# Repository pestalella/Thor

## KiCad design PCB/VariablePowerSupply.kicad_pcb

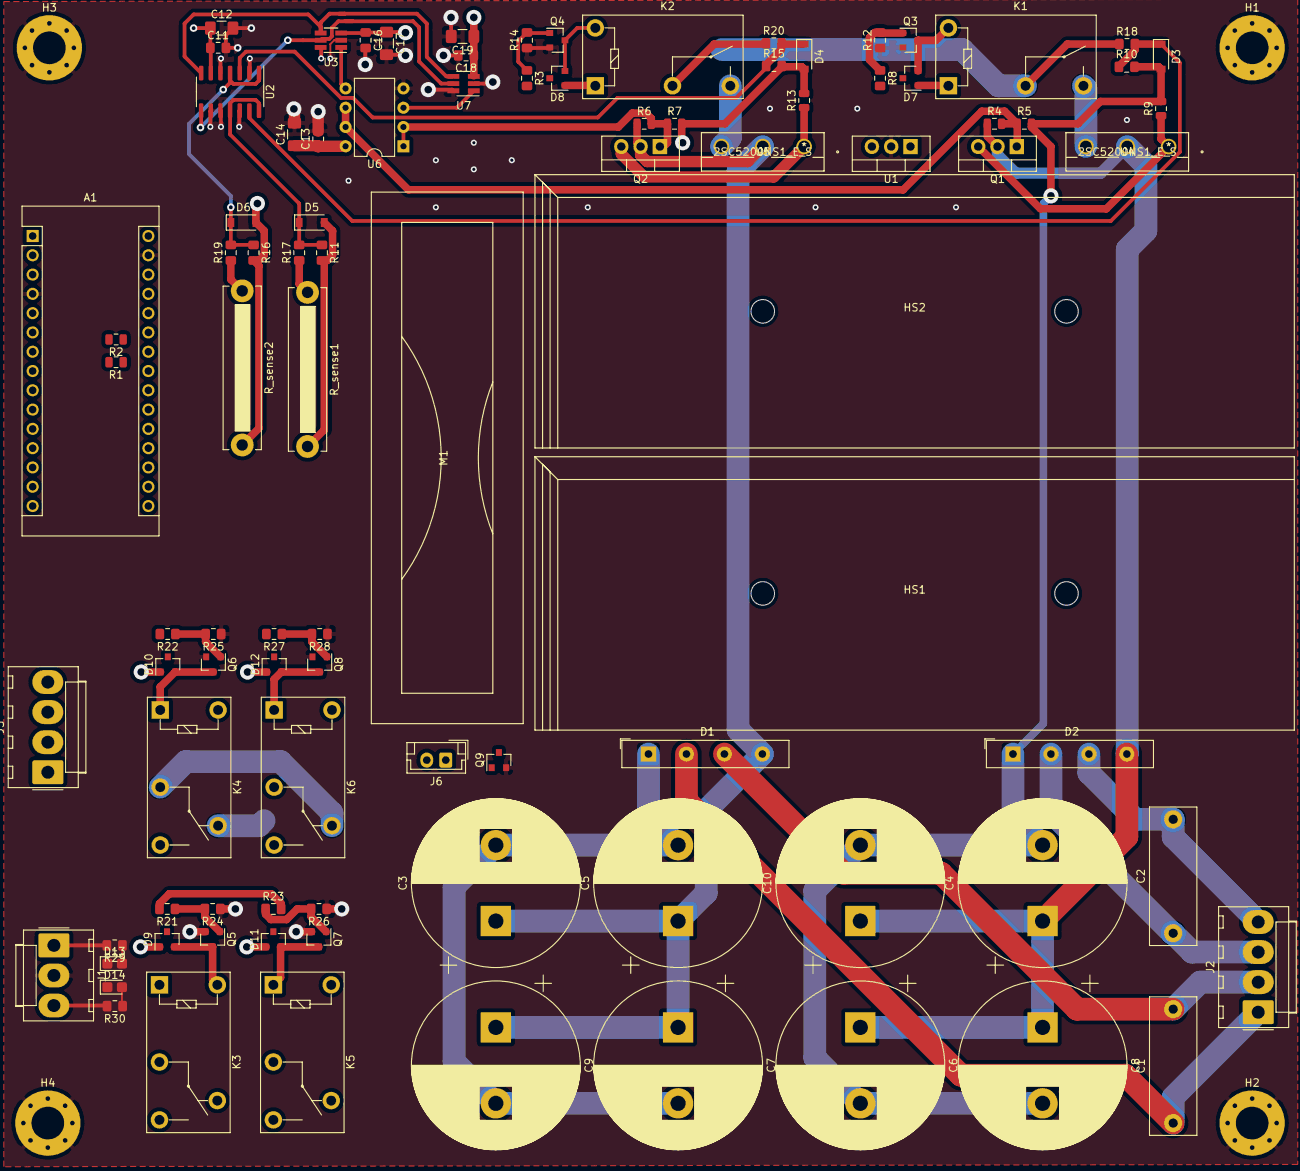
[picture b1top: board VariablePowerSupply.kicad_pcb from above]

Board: 4 copper layers, 98 parts (0 on the bottom side), 55 nets.

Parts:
A1: Arduino_Nano_v2.x; Arduino_Nano
C1, C2: C; C_Rect_L18.0mm_W6.0mm_P15.00mm_FKS3_FKP3
C3, C4, C5, C6, C7, C8, C9, C10: C; CP_Radial_D22.0mm_P10.00mm_SnapIn
C11, C13, C16, C18: 0.1uF; C_0805_2012Metric_Pad1.15x1.40mm_HandSolder
C12, C14, C17, C19: 10uF; C_1206_3216Metric_Pad1.42x1.75mm_HandSolder
D1, D2: D_Bridge_-AA+; Diode_Bridge_22.3x3.5x18.3mm_P5.0mm
D3, D4, D5, D6: 5V1; D_SOD-123
D7, D8, D9, D10, D11, D12: D; SOT-23
D13, D14: LED; LED_0805_2012Metric_Castellated
H1, H2, H3, H4: MountingHole_Pad; MountingHole_4.3mm_M4_Pad_Via
HS1, HS2: Heatsink; Heatsink_100x36mm_2xfixations_HorizAirflow
J1: Conn_01x03_Power_Male; Molex_KK-396_A-41791-0003_1x03_P3.96mm_Vertical
J2, J3: Conn_01x04_Male; Molex_KK-396_A-41791-0004_1x04_P3.96mm_Vertical
J6: Conn_01x02_Male; JST_EH_B2B-EH-A_1x02_P2.50mm_Vertical
K1, K2: Relay_SPST_Panasonic_ALQ305
K3, K4, K5, K6: Relay_SPDT_Panasonic_ALQ105; Relay_SPDT_Panasonic-ALQ105
M1: Fan; Fan_Orion_OD7020_vertical
Q1, Q2: TIP41C; TO-220-3_Vertical
Q3, Q4, Q5, Q6, Q7, Q8: 2N7002E; SOT-23
Q9: TSM2302CX; SOT-23
R1, R2: 4k7; R_0805_2012Metric
R3, R8, R10, R11, R15, R16, R21, R22, R23, R27, R30: 1k; R_0805_2012Metric_Pad1.15x1.40mm_HandSolder
R4, R6: 24k; R_0805_2012Metric
R5, R7: 51k; R_0805_2012Metric
R9, R13: 1k; R_0805_2012Metric
R12, R14, R24, R25, R26, R28: 10k; R_0805_2012Metric_Pad1.15x1.40mm_HandSolder
R17, R18, R19, R20: 9k; R_0805_2012Metric_Pad1.15x1.40mm_HandSolder
R29: 220; R_0805_2012Metric_Pad1.15x1.40mm_HandSolder
R_sense1, R_sense2: 0R1; R_Bare_Metal_Element_L21.3mm_W4.8mm_P20.30mm
U1: LM35-NEB; TO-220-3_Vertical
U2: MCP3428; SOIC-14_3.9x8.7mm_P1.27mm
U3, U7: MCP4725A0T-E_CH; SOT-23-6_Handsoldering
U4, U5: 2SC5200NS1_E_S
U6: LT1490CN8PBF; DIP-8_W7.62mm

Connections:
+5V: A1.3, A1.28, A1.30, C11.1, C12.1, C16.1, C17.1, C18.1, C19.1, D7.1, D8.1, D9.1, D10.1, D11.1, D12.1, J1.1, K1.2, K2.2, K3.2, K4.1, K5.1, K6.1, R1.2, R2.2, R29.2, U1.1, U2.6, U3.3, U3.6, U7.3
+12V: C13.1, C14.1, J1.3, J6.2, R30.2, U6.8
/PWR_A_OUT: K2.4, U5.3
/PWR_B_INTERNAL: K4.4, K6.3
/PWR_B_OUT: K1.4, U4.3
/PWR_B_RET_INTERNAL: K3.5, K5.5
FanControl: A1.6, Q9.1
GND: A1.4, A1.29, C11.2, C12.2, C13.2, C14.2, C16.2, C17.2, C18.2, C19.2, D13.1, D14.1, H1.1, H2.1, H3.1, H4.1, J1.2, Q3.2, Q4.2, Q5.2, Q6.2, Q7.2, Q8.2, Q9.2, R12.1, R14.1, R24.1, R25.1, R26.1, R28.1, U1.2, U2.2, U2.5, U2.9, U2.10, U2.12, U3.2, U6.4, U7.2, U7.6
I2C_SCL: A1.24, R2.1, U2.8, U3.5, U7.5
I2C_SDA: A1.23, R1.1, U2.7, U3.4, U7.4
unnamed: C1.1, D1.2, J2.1
unnamed: C1.2, D1.3, J2.2
unnamed: C2.1, D2.2, J2.3
unnamed: C2.2, D2.3, J2.4
unnamed: D3.1, R10.1, R18.2, U2.13
unnamed: D4.1, R15.1, R20.2, U2.3
unnamed: D5.1, R11.1, R17.2, U2.11, U2.14
unnamed: D6.1, R16.1, R19.2, U2.1, U2.4
unnamed: D7.2, K1.1, Q3.3
unnamed: D8.2, K2.1, Q4.3
unnamed: D9.2, K3.1, Q5.3
unnamed: D10.2, K4.2, Q6.3
unnamed: D11.2, K5.2, Q7.3
unnamed: D12.2, K6.2, Q8.3
unnamed: D13.2, R29.1
unnamed: D14.2, R30.1
unnamed: J6.1, Q9.3
unnamed: Q1.3, R9.1, U4.1
unnamed: Q2.3, R13.1, U5.1
unnamed: Q3.1, R8.1, R12.2
unnamed: Q4.1, R3.1, R14.2
unnamed: Q5.1, R21.1, R24.2
unnamed: Q6.1, R22.1, R25.2
unnamed: Q7.1, R23.1, R26.2
unnamed: Q8.1, R27.1, R28.2
unnamed: U3.1, U6.5
unnamed: U6.3, U7.1
OuputA_enable: A1.9, R3.2
OuputB_enable: A1.10, R8.2
ParallelOutput: A1.8, R21.2, R22.2, R23.2
SeriesOutput: A1.7, R27.2
VAN: J3.3, K3.3, K6.5
VAP: J3.4, K2.3, K4.5, R20.1
VBN: J3.1, K5.4
VBP: J3.2, K6.4
V_controlA: Q2.1, R6.2, R7.1, U6.1, U6.2
V_controlB: Q1.1, R4.2, R5.1, U6.6, U6.7
V_temp: A1.19, U1.3
VccA: C3.1, C5.1, C7.1, C9.1, D1.4, Q2.2, R6.1, U5.2
VccB: C4.1, C6.1, C8.1, C10.1, D2.4, Q1.2, R4.1, U4.2
VeeA: C3.2, C5.2, C7.2, C9.2, D1.1, D4.2, D6.2, R7.2, R13.2, R15.2, R16.2, R_sense2.2
VeeB: C4.2, C6.2, C8.2, C10.2, D2.1, D3.2, D5.2, R5.2, R9.2, R10.2, R11.2, R_sense1.2
VoutAN: K3.4, R19.1, R_sense2.1
VoutBN: K5.3, R17.1, R_sense1.1
VoutBP: K1.3, K4.3, R18.1

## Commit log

2020-07-25 Initial import
2020-07-25 Import existing files
    Import Kicad project, with footprints and schematic. Also import
    some initial Arduino test to interact with the different
    components.
2020-07-25 Add .gitignore and fix README.md
2020-07-25 Added list of features to README.md
2020-07-25 Add the PCB file
2020-07-25 Add more file types to .gitignore
2020-07-27 Multiply opamp output
    The output DAC will only output up to 5V, as it can only be
    powered with up to 5V. This output needs to be multiplied to
    reach 30V to drive the output.
2020-07-27 Add output capacitors
    How could I forget about those?
2021-02-26 Add very preliminary version of VPS FW
    Added temperature reading class and a keyboard reading class.
2021-02-26 Add VSCode config files
2021-02-27 Minor include fixes
2021-02-27 Remove old files
2021-02-28 Add a work journal
    Add the work journal. Add some messages over Serial in order to
    test the Serial output.
2021-03-02 Add rotary encoder support
    Add initial code to support a rotary encoder.

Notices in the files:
parts and their libraries:
Copyright 2016 Accelerated Designs. All rights reserved.
